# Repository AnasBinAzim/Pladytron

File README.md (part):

# **🤖 INTRODUCING TEAM PLADYTRON - WRO 2025**
<div align="center">

</div>

## 👥 **Team PLADYTRON**

| 👤 Name               | 🎓 Institution                          | 📚 Class/Year       | 🎂 Age  |
|----------------------|-----------------------------------------|---------------------|---------|
| **Anas Bin Azim**    | Adamjee Cantonment College              | Class XII           | 17      |
| **SM Mohiuddin Sami**| Rajuk Uttara Model College              | Class XII           | 17      |

---

**Team Origin**: Bangladesh

---

## 🏅 Achievements

- 🥇 **Champion, WRO Bangladesh 2024 (Future Engineers)**
- 🌍 20th place **WRO International in Izmir, Turkey**
- 🛠 Multiple national awards in robotics, AI, and competitive programming contests

---

### 🌟 **The Meaning Behind PLADYTRON**

Our team, “PLADYTRON,” is a perfect blend of technology and imagination—think of Ultron if he had a heart (and wasn’t trying to destroy the world). Inspired by the advanced intelligence of Ultron, we aim to create something truly powerful—but with a lot less existential dread and world domination plans. Plady, on the other hand, is our grounding force, a reminder that even in the world of high-tech innovation, we still know how to laugh, learn, and—let's be honest—mess up a few things along the way.
Behind every project, every line of code, there’s an unseen force—kind of like a secret weapon. And that weapon? The unwavering support of those who stand with us. Their belief in us, quietly powering every step, is the real secret sauce to our success. It’s like having a sidekick in a superhero movie, except instead of a cape, they offer advice, encouragement, and the occasional snack.
Pladytron isn’t just a name—it’s the heart and humor of a shared dream. It’s a place where creativity meets technology, and where the unexpected becomes possible. We’re not just building robots or software—we’re building something that (hopefully) makes the world a little better and a lot more fun. After all, even Ultron had a good idea at first, right?

---

# The Team  

## Anas Bin Azim  

**Age:** 17  

**High School:** Adamjee Cantonment College, Dhaka 

**Description:** Hi! I’m Anas from Bangladesh and this is my second WRO International season. In 2024, I had the honor of representing Team Mayerdoa Robotics at the World Robot Olympiad in Turkey, where we proudly placed 20th in the Future Engineers category. I’ve been deeply involved in robotics for over 4 years, building autonomous systems and competing in both national and international competitions. Beyond robotics, I’m passionate about programming, innovation, quizzing, traveling, and playing cricket]  

---

## Mohiuddin Sami  

**Age:** 17  

**High School:** Rajuk Uttara Model College, Dhaka 

**Description:** Hi! I’m Sayed Md. Mohiuddin Sami from Rajuk Uttara Model College. I’ve been part of the BDOI camp for 2 years and have spent the last 2 years working in robotics and WRO. In 2024, I had the chance to represent Bangladesh at the World Robot Olympiad International Finals in Turkey. I’ve also been doing competitive programming for 4 years, which has helped me grow in problem-solving and logical thinking. Outside of robotics and coding, I enjoy quizzing, traveling, and exploring new ideas.

## 🎉 Project Overview

This repository includes all files, designs, and code for **SMOKI**, our WRO 2024 robot. Below is the folder structure:
Here’s a breakdown of the project folders:

---

## 📑 Table of Contents

- [Code](./Code)  
- [Software Setup](./Software-Setup)  
- [WRO 2024 Future Engineers: Self-Driving Project](./WRO-2024-Future-Engineers-Self-Driving...)  
- [Experiments](./experiments)  
- [Model](./model)  
- [Problems and Solutions](./problemsandsolutions)  
- [Schematic](./schematic)  
- [Source (src)](./src)  
- [t-photos](./t-photos)  
- [v-photos](./v-photos)  
- [Video](./video)  
- [README.md](./README.md)  
---

## Robot Photos (All Directions)

<table>
  <tr>
    <td align="center"><b>Front</b></td>
    <td align="center"><b>Back</b></td>
  </tr>
  <tr>
    <td>
</td>
    <td>
</td>
  </tr>
  <tr>
    <td align="center"><b>Top</b></td>
    <td align="center"><b>Bottom</b></td>
  </tr>
  <tr>
    <td>
</td>
    <td>
</td>
  </tr>
  <tr>
    <td align="center"><b>Left</b></td>
    <td align="center"><b>Right</b></td>
  </tr>
  <tr>
    <td>
</td>
    <td>
</td>
  </tr>
</table>

----

---

### Mission Overview for WRO Future Engineers Rounds

<table>
  <tr>
    <td width="50%" valign="top" align="left">
      <h3>🏁 Round 1: Lap Completion</h3>
      <p>In <strong>Round 1</strong>, the robot must autonomously complete <strong>three laps</strong> on a pre-defined track. The goal of this round is for the bot to demonstrate stable navigation and precise lap tracking without any obstacle avoidance requirements.</p>
      <ul>
        <li><strong>Objective</strong>: Complete three laps on the track within the allotted time.</li>
        <li><strong>Key Tasks</strong>: Accurate path-following, speed control, and lap counting.</li>
      </ul>
      <div align="center">
        <br><br><br><br><br>
        
      </div>
    </td>
    <td width="50%" valign="top" align="left">
      <h3>🏆 Round 2: Lap Completion with Obstacle Avoidance and Parking</h3>
      <p>In <strong>Round 2</strong>, the bot must complete <strong>three laps</strong> while avoiding green and red obstacles:</p>
      <ul>
        <li><strong>Green Obstacles</strong>: The bot should move <strong>left</strong> to avoid.</li>
        <li><strong>Red Obstacles</strong>: The bot should move <strong>right</strong> to avoid.</li>
      </ul>
      <p>After completing the laps, the bot must accurately park within a designated zone.</p>
      <ul>
        <li><strong>Objective</strong>: Complete three laps, avoid obstacles, and park in the designated area.</li>
        <li><strong>Tasks</strong>: Obstacle detection, color-based avoidance, and precision parking.</li>
      </ul>
      <div align="center">
        
      </div>
    </td>
  </tr>
</table>

---
>[!IMPORTANT]
>**Important: WRO Future Engineers Rulebook**
>* **Thorough Reading:** Ensure that you thoroughly read the **WRO Future Engineers 2024 Rulebook** to understand all rules and guidelines.
>* **Official Link:** Access the rulebook here: [🔗 WRO Future Engineers 2024 Rulebook](https://wro-association.org/competitions/future-engineers/).

---
---

## 🧩 Components and Hardware
Our bot is equipped with various components that support its autonomous functionality. Here is a breakdown of the key hardware elements used in this project:

| Component                  | Description                                                                                      | Image                          | Purchase Link                                                                                  |
|----------------------------|------------------------------------------------------------------------------------------------|--------------------------------|-----------------------------------------------------------------------------------------------|
| **Chassis - Custom Made**   | Custom-designed chassis tailored to fit all components and optimize stability and movement.    | <div align="center"></div>         | N/A                                                                                           |
| **RPLIDAR C1**             | 360-degree laser scanner used for mapping and obstacle detection.                              | <div align="center"></div>                   | [Purchase RPLIDAR C1](https://www.mybotshop.de/SLAMTEC-RPLIDAR-C1-360-Laser-Scanner-12-m)     |
| **Servo Motor SG90**       | Small, lightweight servo motor used for precise control of angles and positioning.             | <div align="center"></div>             | [Purchase SG90](https://bongotech.ai/product/sg90-micro-servo-motor-180-degree)                |
| **SJ CAM C200**            | Captures visual data, supporting navigation and obstacle detection tasks.                      | <div align="center"></div>                  | [Purchase SJ CAM C200](https://amzn.to/3SJCAM) (From previous knowledge)                      |
| **Buck Module XL4016**     | Provides stable voltage regulation for power management.                                      | <div align="center"></div>           | [Purchase XL4016](https://amzn.to/4xl4016) (From previous knowledge)                          |
| **Motor Driver L293D**     | Dual H-Bridge motor driver for controlling DC motors and stepper motors.                       | <div align="center"></div>           | [Purchase L293D](https://electropeak.com/l293d-motor-drive-shield)                            |
| **Booster Module 5V to 40V** | Voltage booster module to step up power supply from 5V to 40V, supporting high-voltage requirements. | <div align="center"></div>       | [Purchase Booster Module](https://robu.in/product-category/electronic-modules/electronic-module/buck-boost-converter/boost-converter/) |

# Mobility Management :

#### 🛠️ Chassis Assembly Process

## CHASSIS FIRST FLOOR : 

This is the first floor of the robot chassis, designed to serve as the primary structural layer of the bot. The STL model shows a flat base plate with multiple precisely positioned mounting holes and slots for components.

Key Features:

Steering Shaft Mount: The elongated slot at the top center is designed to hold the steering shaft, ensuring smooth and stable movement.

Servo Motor Mount: Dedicated mounting holes allow the servo motor to be securely attached for steering control.

Camera Holder: The central cut-out and surrounding structure provide space for installing a camera for vision-based navigation.

Wheel Mounts: Side holes are aligned to support the wheels, making them properly fixed to the frame.

Base Support: This floor acts as the foundation of the robot, supporting the upper floors and ensuring stability during operation.

Dimensions:

Width (X): 101.5 mm

Length (Y): 185.0 mm

Thickness (Z): 10.0 mm

---
---

### CHASSIS STEERING :

This is the steering plate of the robot chassis, designed to integrate with the first floor and provide precise steering control. The central rectangular gap is a servo clearance slot, which allows the servo horn and linkage to move freely during steering. The smaller holes around the center are meant for mounting the servo securely, while the larger side holes provide attachment points to connect the steering plate with the rest of the chassis. The plate is compact yet durable, ensuring stability during turns, and it directly connects the servo motor to the steering shaft and wheels, making it an essential component for controlling the robot’s movement.

Dimensions:

Width (X): 96.2 mm

Height (Y): 35.55 mm

Thickness (Z): 10 mm

---
---

### STEERING SHAFT :

This part is the steering shaft of the robot chassis. It connects directly to the steering plate and transmits the motion from the servo motor to the wheels, enabling controlled directional movement. The design includes a central body with mounting cut-outs and side holes that allow it to be fixed securely to the chassis while maintaining free rotational movement where needed. Its sturdy build ensures that torque from the servo is effectively transferred to the wheels without bending or slipping, making it a key component for precise steering.

Dimensions:

Width (X): 

Height (Y): 

Thickness (Z): 

---
---

## CHASSIS SECOND FLOOR :

This is the second floor of the robot chassis, designed to mount the following components:

RPLIDAR C1 (with a 10 cm clearance ensured by floor orientation)

LiPo 1500mAh 9A 3S battery

STL Dimensions: 131.27 mm × 101.50 mm × 10.00 mm

The plate includes cutouts for weight reduction and cable management, along with mounting holes for secure installation. Its orientation was carefully adjusted to provide the RPLIDAR with optimal clearance for unobstructed 360° scanning.

---

## CHASSIS TOP FLOOR:

Top & 3rd Floor – Electronics Section

This floor of the chassis holds the core electronic components required for power regulation and motor control.

Components

Raspberry Pi 4B – Acts as the main controller, handling computation, control logic, and communication.

XL4016 Buck Converter – Steps down the LiPo battery voltage to the levels required by the Raspberry Pi and other electronics.

L293D Motor Driver – Provides motor control by supplying the necessary current and voltage to the DC motors.

Power Switch – Allows safe shutdown and startup of the electronics.

Veroboard – Serves as the wiring platform, connecting the Raspberry Pi, buck converter, motor driver, and switch.

Functionality

The LiPo battery powers the system.

The buck converter regulates the voltage for stable Raspberry Pi operation.

The L293D motor driver interfaces between the Raspberry Pi and the motors, enabling directional control.

The veroboard ensures secure and organized wiring between all components.

The switch provides overall power control for the floor.

---
---

>[!IMPORTANT]
> ALL THE STL AND DXF FILES ARE PROVIDED IN THE MODEL SECTION AND A PREVIEW OF THE WHOLE THING COMBINED IS GIVEN BELOW.
---

# TOTAL PREVIEW:

## Model Views

<table>
  <tr>
    <td align="center"><b>Top</b></td>
    <td align="center"><b>Bottom</b></td>
  </tr>
  <tr>
    <td>

</td>
    <td>
</td>
  </tr>
  <tr>
    <td align="center"><b>Left</b></td>
    <td align="center"><b>Right</b></td>
  </tr>
  <tr>
    <td>
</td>
    <td>
</td>
<tr>
    <td align="center"><b>Tilt1</b></td>
    <td align="center"><b>Tilt2</b></td>
  </tr>
  <tr>
    <td>
</td>
    <td>

</td>
  </tr>

</table>

---
---

# Mobility Management:

The mobility system of our robot has been meticulously designed to ensure smooth, efficient, and reliable movement, addressing both power distribution and maneuverability. This section outlines the evolution of our robot's mobility systems, including upgrades to the steering and gear systems.

---

#### **16GA 800 RPM DC Gear Motor**

<table>
<tr>
<td width="50%">
<div align="center">

</div>
</td>
<td width="50%">

A **16GA DC gear motor** is a DC motor with an integrated gearbox. It provides controlled shaft rotation with increased output torque through gearbox reduction.

##### **How the Motor Works**
- The DC motor converts electrical input into rotational motion of the armature and shaft.  
- The gearbox stages reduce output speed and increase torque at the output shaft.  
- The D-flat on the shaft provides a positive mechanical interface for gears, pulleys, or couplings.

##### **Specifications**
- **Rated Speed:** 800 RPM  
- **Shaft Diameter:** 3.0 mm (D-flat: 2.5 mm)  
- **Gearbox Diameter:** 16 mm  
- **Gearbox Length:** 14 mm  
- **Motor Body Length:** 26.5 mm  
- **Shaft Length (protruding):** 11.2 mm

##### **Advantages**
1. **Compact Design**: Small gearbox diameter and short overall length for tight assemblies.  
2. **Increased Torque**: Gear reduction delivers higher torque at the output shaft for loaded conditions.  
3. **Positive Shaft Interface**: D-flat prevents rotary slip when fitted with set-screws or couplings.

</td>
</tr>
</table>

---

### **Rear Axle Power Distribution**

Initially, the rear wheels were powered through a **Bevel Gear**, but we later upgraded to a **Differential Gearbox** to improve efficiency and performance during turns.

---

#### **Bevel Gear**

<table>
<tr>
<td width="50%">
<div align="center">
  
</div>
</td>
<td width="50%">

A **bevel gear** is a type of gear where the axes of the two shafts intersect, and the tooth-bearing faces of the gears are conical. Bevel gears are commonly used to transfer motion between intersecting shafts at an angle, typically 90°.

##### **How Bevel Gears Work**
- A driver gear transfers motion to a driven gear, which rotates an output shaft.
- The teeth of the gears are designed to mesh smoothly, transferring torque efficiently between the shafts.

##### **Advantages of Bevel Gears**
1. **Compact Design**: Suitable for space-constrained applications.
2. **Efficient Torque Transfer**: Provides reliable power transmission at angles.
3. **Versatility**: Can operate at angles other than 90° if needed.

</td>
</tr>
</table>

---
>[!IMPORTANT]
> Bevel gears were essential in the initial stages of our design, but they had limitations in terms of energy efficiency during turns.
---

#### **Differential Gearbox**

<table>
<tr>
<td width="50%">

A **differential gearbox** allows the wheels on the same axle to rotate at different speeds while receiving power from a single motor. This is crucial for smooth turning, where the outer wheel must travel a larger distance than the inner wheel.

##### **Advantages of Differential Gearbox**
1. **Smooth Turns**: Adapts to varying wheel speeds, ensuring efficient cornering.
2. **Energy Efficiency**: Reduces energy wastage by minimizing wheel slippage.
3. **Component Longevity**: Minimizes wear on tires and axles.

##### **How Differential Gears Work**
- Power from the motor is delivered to an input shaft.
- The differential splits the torque between the two wheels via bevel or spider gears inside the housing.
- During turns, the differential allows one wheel to spin faster than the other, ensuring smooth movement.

</td>
<td width="50%">
<div align="center">
  
</div>
</td>
</tr>
</table>

---

### **Servo Motor with L293D Motor Driver**

<table>
<tr>
<td width="30%">
<div align="center">
  
</div>
</td>
<td width="70%">

We used the **L293D Motor Driver** in combination with a **Servo Motor** to control the robot's wheels effectively. The L293D is a dual H-Bridge motor driver that is perfectly suited for the LEGO motor, which operates at **750mA** current.

##### **Why L293D?**
- **Optimal Current Capacity**: Can handle up to **1A** peak current, suitable for the LEGO motor’s 750mA requirement.
- **Bidirectional Control**: Facilitates forward and backward motion of the wheels.
- **Compact and Lightweight**: Ideal for small-scale robotic systems.
- **PWM Support**: Enables smooth speed control of the motors.

##### **Advantages of the Servo Motor with L293D**
1. **Accurate Steering**: The servo motor ensures precise angle adjustments.
2. **Smooth Speed Control**: PWM functionality provides variable speed control.
3. **Efficient Current Management**: Matches the LEGO motor's current needs, ensuring reliable operation.

</td>
</tr>
</table>

---

#### **Comparison: Bevel Gear vs. Differential Gearbox**

| **Feature**                | **Bevel Gear**                            | **Differential Gearbox**                |
|----------------------------|-------------------------------------------|-----------------------------------------|
| **Turning Efficiency**     | Limited; fixed wheel speeds.             | Superior; wheels rotate independently. |
| **Energy Usage**           | Higher due to slippage during turns.     | Lower; optimized for dynamic turns.    |
| **Durability**             | Higher strain on components.             | Reduced strain; longer component life. |

---

### **Steering Systems**

The robot was first designed with an Ackermann Steering System, which is widely recognized for its efficiency in full-scale vehicles where smooth and realistic cornering is important. This system was chosen because it closely replicates how cars steer, making it ideal for projects that aim to simulate real-world vehicle dynamics. However, as the design of the robot progressed, the steering system was later replaced with a LEGO-based steering mechanism. The change was made to simplify construction, reduce complexity, and improve modularity, all while maintaining effective and reliable steering control. The LEGO steering setup makes it easier to experiment, repair, and scale the design without sacrificing too much performance, which is an important advantage in prototyping and educational robotics.

The Ackermann Steering System itself is a clever mechanical arrangement that ensures each wheel follows a natural path while the vehicle turns. In any cornering situation, the inner wheels of a vehicle must rotate at a sharper angle than the outer wheels because they travel along a smaller radius. Without this adjustment, wheels would slip or drag, leading to wasted energy and uneven motion. The Ackermann geometry solves this by connecting the front wheels through steering arms angled in such a way that the imaginary extension of these arms intersects at the center of the turn’s radius. This alignment ensures that all wheels follow concentric paths, allowing the vehicle to turn smoothly and efficiently without excessive tire wear or unnecessary power loss.

In practice, the Ackermann system has several clear advantages for robotic applications. It minimizes slippage between the wheels and the ground, which results in more efficient turning and better energy conservation. The reduction of wheel drag also means that the motors driving the vehicle consume less power during maneuvers, which is especially valuable in battery-powered robots where energy efficiency extends operating time. Another key benefit is that it provides a highly realistic simulation of how cars steer, making it particularly useful for robotics projects that aim to mimic real-world automotive systems or serve as educational platforms to demonstrate fundamental vehicle dynamics. Although our project ultimately transitioned to a LEGO-based steering approach for modularity and ease of construction, the principles and advantages of Ackermann steering remain highly relevant for anyone interested in understanding efficient and practical steering systems in robotics and beyond.

---
---

## **SERVO MOTOR :** 
# Servo Motor - Tower Pro MG90S

<table>
  <tr>
    <td>
      
    </td>
    <td>
      <h3>Specifications</h3>
      <ul>
        <li><strong>Weight:</strong> 13.4g</li>
        <li><strong>Stall torque:</strong> 2.2 kgf·cm (6V)</li>
        <li><strong>Operating speed:</strong> 0.08 s/60° (6V)</li>
        <li><strong>Rotation angle:</strong> 120°</li>
        <li><strong>Gear type:</strong> Metal gears</li>
        <li><strong>Operating voltage:</strong> 4.8V – 6V</li>
      </ul>
    </td>
  </tr>
</table>

---

The Tower Pro MG90S is a micro servo motor designed for applications where compact size and high torque are required, making it a reliable choice for robotics, RC models, and automation projects. Built with durable metal gears, it offers a longer operational lifespan compared to plastic-geared alternatives, while maintaining a lightweight 13.4g profile that makes it easy to integrate into small-scale designs. Operating on a voltage range of 4.8V to 6V, it delivers up to 2.2 kgf·cm stall torque and a quick 0.08s/60° response at 6V, ensuring both strength and speed for demanding tasks. With a rotation range of 120°, the MG90S provides precise angular control suitable for robotic arms, pan-tilt camera gimbals, or steering systems in miniature vehicles. Its compatibility with standard PWM signals means it can be driven directly by most microcontrollers, including Arduino and Raspberry Pi, without the need for additional hardware. Engineers and hobbyists often choose the MG90S because it balances performance and durability in a very small form factor, making it a practical and cost-effective solution for projects that require accurate movement and dependable performance under continuous load.

---

## Where to Buy

You can purchase the servo motor here:  
👉 [Tower Pro MG90S - Cleste.ro](https://cleste.ro/motor-servo-mg90s-180g.html)

## SERVO-HOLDER :

### SG90 / MG90 Servo Holder

This is a **servo motor holder/mount** designed for **SG90** and **MG90S micro servos**.  
It provides a secure and stable way to fix the servo motor onto different surfaces such as a robot chassis, acrylic base, or wooden frame.

---

## Description
## Servo Motor Holder / Mount (SG90 & MG90S)

This servo motor holder is designed specifically for the popular SG90 and MG90S micro servos, providing a secure and reliable way to mount the motor onto different surfaces such as a robot chassis, acrylic base, or even wooden frames. The primary goal of the mount is to eliminate instability and vibration, ensuring that the servo can deliver accurate and repeatable movements during operation. For small-scale robotics and automation projects where precision matters, this holder becomes an essential accessory.
The base of the mount is a flat rectangular plate equipped with four mounting holes that allow it to be firmly attached using screws or bolts. This rigid foundation ensures that once the holder is installed, it remains stable and does not shift under load, even when the servo is driving linkages or mechanical arms. At the center of the design, there is a servo housing slot carefully dimensioned to snugly fit SG90 and MG90S servos. This slot prevents any side-to-side play and keeps the servo perfectly aligned, which is important when the servo is used for steering mechanisms, grippers, or robotic arms where accuracy of angular motion is critical.
On the sides of the housing are clamp sections with additional screw holes, which allow the servo to be tightly locked in place once inserted. This design makes sure the servo remains fixed during continuous operation, preventing unwanted movement that could lead to mechanical inaccuracy or wear. At the front, the mount features an open clearance space that allows the servo horn or arm to rotate freely without obstruction. This ensures that the servo’s full range of motion can be utilized, whether it is controlling wheels, levers, or pan-tilt systems.

The bottom of the mount is left open to provide space for the servo’s wiring to pass through. This prevents cable bending and stress at the connector, reducing the risk of damage to the wires over time and allowing easy integration into compact robotic builds. By providing both mechanical stability and practical cable management, the holder is designed to extend the lifespan of the servo and improve overall reliability of the system.

In terms of material, PLA is often sufficient for hobby projects where light loads and indoor conditions are expected. However, for applications requiring greater durability or exposure to outdoor environments, PETG or ABS is recommended since both materials offer improved toughness and resistance to stress compared to PLA. The mount’s design is fully compatible with Tower Pro SG90 and MG90S servos, making it versatile for use across a wide range of robotic and automation projects where these micro servos are commonly deployed.

---
---
# ⚡ Power and Sense Management

The **Power and Sense Management** system of our robot has been meticulously designed to optimize performance while ensuring reliable power delivery, precise sensing, and efficient communication between components.
# Battery: Gens Ace Airsoft 3S Li-Po Battery (11.1V 1500mAh 35C)

<table>
  <tr>
    <td>
      
    </td>
    <td>
      <h3>Specifications</h3>
      <ul>
        <li><strong>Brand:</strong> Gens Ace Airsoft</li>
        <li><strong>Battery Type:</strong> Li-Po (Lithium Polymer)</li>
        <li><strong>Nominal Voltage:</strong> 11.1V (3S)</li>
        <li><strong>Capacity:</strong> 1500 mAh</li>
        <li><strong>Energy:</strong> 16.65 Wh</li>
        <li><strong>Discharge Rate:</strong> 35C</li>
        <li><strong>Connector Type:</strong> T-Plug / Deans Connector</li>
        <li><strong>Balance Plug:</strong> JST-XH</li>
        <li><strong>Weight:</strong> ~120g</li>
      </ul>
    </td>
  </tr>
</table>

---

The **Gens Ace 3S Li-Po battery** is a lightweight and powerful energy source designed for high-performance robotics, drones, RC vehicles, and airsoft equipment.  
With a **capacity of 1500mAh** and a **35C discharge rating**, it delivers consistent current output suitable for motors, sensors, and controllers that require stable power.  
Its **compact size and low weight** make it easy to integrate into mobile robotic platforms.  
The built-in **Deans/T-Plug connector** ensures low-resistance power delivery, while the **JST-XH balance connector** allows for safe charging and cell balancing.  

This battery is ideal for applications requiring **high burst currents, reliability, and long cycle life**, making it a solid choice for powering small-to-medium robotics systems.

---

# **Microcontroller :**  
# Raspberry Pi 4 Model B

<table>
  <tr>
    <td>
      
    </td>
    <td>
      <h3>Specifications</h3>
      <ul>
        <li><strong>Processor:</strong> Broadcom BCM2711, Quad-core Cortex-A72 (ARM v8) 64-bit SoC @ 1.5GHz</li>
        <li><strong>RAM Options:</strong> 2GB, 4GB, or 8GB LPDDR4-3200 SDRAM</li>
        <li><strong>Networking:</strong> Gigabit Ethernet, 2.4GHz & 5.0GHz 802.11ac Wi-Fi, Bluetooth 5.0</li>
        <li><strong>USB Ports:</strong> 2 × USB 3.0, 2 × USB 2.0</li>
        <li><strong>Video & Sound:</strong> 2 × micro-HDMI ports (up to 4Kp60), MIPI DSI display port, MIPI CSI camera port</li>
        <li><strong>Storage:</strong> microSD card slot for OS and data storage</li>
        <li><strong>GPIO:</strong> 40-pin header, backward-compatible with previous Raspberry Pi boards</li>
        <li><strong>Power:</strong> 5V DC via USB-C connector (minimum 3A)</li>
        <li><strong>Dimensions:</strong> 85.6mm × 56.5mm</li>
      </ul>
    </td>
  </tr>
</table>

---

The **Raspberry Pi 4 Model B** is a powerful single-board computer that serves as the main controller of the robot.  
It offers significant improvements over previous models, including a faster **quad-core ARM Cortex-A72 CPU**, more memory options, dual micro-HDMI outputs supporting **dual 4K displays**, and faster networking with **true Gigabit Ethernet** and **dual-band Wi-Fi**.  
Its 40-pin GPIO header provides compatibility with a wide range of sensors, motor drivers, and other modules, making it extremely versatile for robotics and IoT applications.  

Thanks to its **USB 3.0 ports**, it can interface with high-speed peripherals such as cameras, LIDAR sensors, or external storage, while the **USB-C power input** ensures stable operation.  
In this project, the Raspberry Pi 4B acts as the **central brain**, handling computer vision, path planning, and high-level decision-making, while coordinating with microcontrollers, sensors, and actuators to control the entire robot.

---

## **GPIO PINOUT OF RPI 4B** : 

# Raspberry Pi 4 Model B GPIO (40-pin Header)

<table>
  <tr>
    <td>
      
    </td>
    <td>
      <h3>Specifications</h3>
      <ul>
        <li><strong>Total Pins:</strong> 40 (2×20 header)</li>
        <li><strong>Power Pins:</strong> 2 × 5V, 2 × 3.3V, 8 × Ground (GND)</li>
        <li><strong>GPIO Pins:</strong> 26 (configurable as input/output)</li>
        <li><strong>Dedicated Interfaces:</strong> 
          <ul>
            <li>UART (TXD, RXD)</li>
            <li>SPI (MOSI, MISO, SCLK, CE0, CE1)</li>
            <li>I²C (SDA, SCL)</li>
            <li>PWM channels</li>
          </ul>
        </li>
        <li><strong>Voltage Levels:</strong> 3.3V logic (NOT 5V-tolerant)</li>
        <li><strong>Backward Compatibility:</strong> Same pinout as Raspberry Pi 3B/3B+</li>
      </ul>
    </td>
  </tr>
</table>

---

The **Raspberry Pi 4B GPIO header** provides 40 pins that allow direct hardware interfacing with sensors, actuators, and external modules.  
Among these are multiple **power pins (5V and 3.3V)**, **ground pins**, and **26 flexible GPIO pins** which can be programmed as input or output using libraries such as **RPi.GPIO** or **GPIO Zero**.  

The header also exposes dedicated hardware interfaces, including **UART for serial communication**, **SPI for high-speed device connections**, and **I²C for multi-sensor integration**, along with PWM support for driving **motors, LEDs, and servos**.  

Because the pins operate at **3.3V logic levels**, external level shifters are required when interfacing with 5V components.  
This GPIO header is the bridge between the Raspberry Pi and the physical world, making it an essential feature for robotics, IoT, and embedded system projects.

---
---

## **BUCK CONVERTER** (8.4 TO 5V) : 
### XL4016 DC-DC Step-Down Module

<table>
  <tr>
    <td>
      
    </td>
    <td>
      <h3>Specifications</h3>
      <ul>
        <li><strong>Chipset:</strong> XL4016E1 DC-DC Buck Converter</li>
        <li><strong>Input Voltage:</strong> 8V – 36V DC</li>
        <li><strong>Output Voltage:</strong> 1.25V – 32V DC (adjustable)</li>
        <li><strong>Output Current:</strong> Up to 8A (continuous), 12A peak</li>
        <li><strong>Conversion Efficiency:</strong> Up to 95%</li>
        <li><strong>Switching Frequency:</strong> ~180 kHz</li>
        <li><strong>Protections:</strong> Over-current, thermal shutdown</li>
        <li><strong>Heat Dissipation:</strong> Integrated heatsink for stability under high load</li>
        <li><strong>Dimensions:</strong> 60mm × 52mm × 20mm (approx.)</li>
      </ul>
    </td>
  </tr>
</table>

---

The **XL4016 buck converter** is a high-power DC–DC step-down module designed to provide stable and efficient voltage regulation for robotics, automation, and embedded systems. With an input range of 8–36V and an adjustable output from 1.25–32V, it is highly versatile and can power a wide variety of subsystems from a single battery source. Its ability to deliver up to **8A of continuous current** (with peaks of 12A) makes it suitable for driving motor controllers, Raspberry Pi boards, and other current-hungry electronics simultaneously. The module achieves up to 95% efficiency, reducing energy losses and minimizing heat buildup. The integrated heatsink ensures stable operation even under heavy loads, while built-in protection circuits safeguard against over-current and thermal issues. For robotics applications, the XL4016 is often recommended because it allows a single Li-Po or Li-ion battery pack to be safely stepped down to multiple regulated voltages, ensuring reliable operation of both logic-level electronics and power-hungry actuators.

---

## **Sensor :**  
# MPU-6050 6-Axis Gyroscope and Accelerometer

<table>
  <tr>
    <td>
      
    </td>
    <td>
      <h3>Specifications</h3>
      <ul>
        <li><strong>Chipset:</strong> InvenSense MPU-6050</li>
        <li><strong>Sensor Type:</strong> 3-axis gyroscope + 3-axis accelerometer</li>
        <li><strong>Operating Voltage:</strong> 3V – 5V</li>
        <li><strong>Communication Interface:</strong> I²C (default address 0x68)</li>
        <li><strong>Gyroscope Range:</strong> ±250, ±500, ±1000, ±2000 °/s</li>
        <li><strong>Accelerometer Range:</strong> ±2g, ±4g, ±8g, ±16g</li>
        <li><strong>Sampling Rate:</strong> Up to 1 kHz</li>
        <li><strong>Digital Motion Processor (DMP):</strong> Built-in for sensor fusion</li>
        <li><strong>Dimensions:</strong> ~20mm × 15mm × 2mm (module size varies)</li>
      </ul>
    </td>
  </tr>
</table>

---

The **MPU-6050** is a 6-axis motion tracking sensor that integrates a **3-axis gyroscope** and a **3-axis accelerometer** on a single chip, making it one of the most widely used sensors in robotics and embedded systems. It communicates via the I²C protocol, which allows it to connect easily to microcontrollers like the Arduino, ESP32, or Raspberry Pi. The sensor provides motion data across multiple selectable ranges, with gyroscope sensitivity from ±250 to ±2000 degrees per second and accelerometer ranges from ±2g to ±16g. This versatility makes it suitable for detecting orientation, angular velocity, and linear acceleration in real time. The built-in **Digital Motion Processor (DMP)** can handle sensor fusion internally, combining gyro and accelerometer data to output stable orientation values, reducing the computational load on the main controller. For robotics, the MPU-6050 is commonly used in balancing robots, drones, navigation systems, and motion-controlled projects, where accurate and responsive motion sensing is essential for stability and control.

---

## **Camera :**  
# SJCAM C200 Action Camera

<table>
  <tr>
    <td>
      
    </td>
    <td>
      <h3>Specifications</h3>
      <ul>
        <li><strong>Sensor:</strong> 4K CMOS image sensor</li>
        <li><strong>Video Resolution:</strong> 4K @ 24fps, 2K @ 30fps, 1080p @ 60fps</li>
        <li><strong>Photo Resolution:</strong> Up to 16MP</li>
        <li><strong>Lens:</strong> 154° wide-angle lens</li>
        <li><strong>Display:</strong> 1.3-inch front screen + status indicators</li>
        <li><strong>Battery:</strong> 1200mAh (removable, USB-C charging)</li>
        <li><strong>Connectivity:</strong> Wi-Fi, USB-C</li>
        <li><strong>Storage:</strong> MicroSD card up to 128GB</li>
        <li><strong>Waterproof:</strong> Up to 5m without case, 30m with case</li>
        <li><strong>Dimensions:</strong> ~68mm × 32mm × 26mm</li>
      </ul>
    </td>
  </tr>
</table>

---

The **SJCAM C200** is a compact 4K action camera designed for high-quality video and photo capture in robotics, drones, and field-testing environments. It features a **154° wide-angle lens**, making it well-suited for wide field-of-view applications such as navigation, mapping, and vision-based obstacle detection. The camera supports recording at multiple resolutions, including **4K at 24fps** and **1080p at 60fps**, giving flexibility between image detail and frame rate depending on the task. With a removable **1200mAh battery** and **USB-C charging**, it provides convenient power management, while Wi-Fi connectivity allows real-time preview and data transfer to companion devices. Its rugged design makes it waterproof up to 5m without housing and up to 30m with an additional case, ensuring reliable performance in outdoor and challenging environments. For robotics projects, the SJCAM C200 is an excellent choice as a vision module, balancing portability, durability, and high-definition imaging in a small and versatile package.
---
---

# *PCB*  
## Previous PCB Design and Power Distribution  

| **Top View of PCB** | **Bottom View of PCB** | **Power Management Diagram** |
|----------------------|------------------------|-------------------------------|
|  |  |  |

---

The PCB shown above was designed as the **central power management and distribution unit** for the robot, ensuring that every subsystem received the correct voltage and current for stable operation. The board draws power from two **Lithium-Ion cells**, each rated at 4.2V, providing a combined supply of **8.4V** when fully charged. This input is then carefully regulated using multiple DC–DC converters to meet the diverse requirements of the system.  

At the heart of the regulation stage, an **XL4016 buck converter** steps the 8.4V battery voltage down to a stable **5V rail**, which powers the **Raspberry Pi 5** and other core electronics. Additional buck converter modules are integrated to provide subsystem-specific voltages: one module regulates to **6V for the servo motor**, while another supplies **5V dedicated to the ESP32 microcontroller**, ensuring isolation and consistent operation. For the high-power motors, the PCB incorporates a **buck-boost converter** that outputs **12V**, guaranteeing reliable torque and speed even as the battery voltage drops during operation.  

This combination of regulated rails allows the robot to operate multiple controllers, sensors, and actuators from a single compact PCB without instability or power loss. By integrating switching converters and carefully routing the distribution, the board minimizes heat, maximizes efficiency, and protects sensitive comp
onents from voltage fluctuations. Overall, this design highlights the importance of structured power management in robotics, where both logic-level devices and power-hungry actuators must coexist seamlessly on the same platform.

---
# *CurrentPCB* :

Compared to our earlier design, the new PCB introduces several improvements aimed at stability, modularity, and ease of use. The earlier version primarily served as a basic power distribution board with buck converters and minimal control features. In this revised version, additional attention has been given to **structured wiring via ribbon connectors**, improved **switching and manual control through a larger rocker and push button**, and **better integration of the buck converter section** with heat dissipation. The placement of capacitors, inductor coil, and screw terminals has been optimized for cleaner power flow, and the routing now reduces noise and voltage drops across the board. Overall, the new design is more robust, reliable, and serviceable compared to the prototype.  

# *CIRCUITDIAGRAM* :

# Explanation:

This circuit integrates the Raspberry Pi GPIO header with a set of sensors, actuators, and motor driver modules, forming the control and power distribution system for a small robot. The Raspberry Pi acts as the central controller, sending signals to motors, servos, and indicators while also receiving sensor feedback to make decisions in real time.
At the top of the diagram, we see the Raspberry Pi GPIO pinout, which is the core interface between the Pi and external devices. Each pin can be configured as an input or output, supplying logic-level signals (3.3V) that control the connected hardware. The Pi provides 5V and 3.3V power rails, as well as ground connections, which are distributed to all modules in the circuit.
A servo motor is connected to the Pi using three wires: VCC (power), GND (ground), and the SIGNAL pin, which is linked to one of the Pi’s PWM-enabled GPIO pins. This allows the Pi to control the servo angle precisely using PWM (Pulse Width Modulation). Servos are typically used for steering mechanisms or angular adjustments in robots, so this one is likely managing the robot’s front wheel alignment or a pan/tilt system.
On the left side of the circuit, a push button and an LED are wired into the GPIO header. The push button is used as a digital input — when pressed, it connects the GPIO pin to ground, sending a low signal to the Pi. This can be used for resets, mode changes, or manual overrides. The LED, on the other hand, is controlled through a GPIO pin as an output. It provides visual feedback, such as power status, errors, or activity indicators, allowing the operator to easily monitor the robot’s state.
At the bottom, the L293D motor driver IC is connected between the Pi and a DC motor. The Pi itself cannot supply enough current to directly drive motors, so the L293D acts as a buffer and amplifier. It uses the low-current logic signals from the Pi to control the higher-current flow from the battery to the motor. This enables bidirectional motor control (forward and backward rotation) and also supports PWM for speed regulation. In this configuration, the motor shown is most likely one of the drive motors that moves the robot’s wheels.
On the right side, we see an MPU-6050 IMU (Inertial Measurement Unit) connected via I²C communication. The SDA (data) and SCL (clock) lines run from the Pi’s GPIO header to the sensor module, with VCC and GND providing power. The MPU-6050 combines a 3-axis gyroscope and a 3-axis accelerometer, which together measure angular velocity and linear acceleration. This data is essential for balance, orientation, and navigation, particularly in robots that need to track their motion or maintain stability on uneven terrain.
Next to it is a buck converter module (with a heatsink and inductor coil). This component regulates the battery voltage down to safe levels required by the Raspberry Pi, motors, and sensors. Since motors can cause voltage fluctuations when they start or stop, the buck converter ensures that the Pi always receives a clean and stable supply. The input of the buck converter comes directly from the main battery (Li-ion cells), and the outputs are distributed to different subsystems: 5V for the Pi and ESP32, 6V for the servo, and 12V (via buck-boost regulation) for the motors.
The wiring shows how all the power rails (red for positive, black for ground, and green/yellow/orange for signals) are carefully routed to prevent noise and maintain clear separation between logic-level signals and high-current motor wiring. The Pi orchestrates everything: it reads the sensor data from the MPU-6050, processes input from the push button, controls the LED for feedback, drives the servo motor with PWM, and commands the DC motor through the L293D motor driver.

---
# *SCHEMATIC FOR THE NERDS* : 

###  Camera Placement and Functionality

The robot's main camera is positioned at the top and angled slightly downwards. This setup enhances object detection capabilities by providing:
- **🔍 Close-Range Detection**: The camera can identify objects in close proximity with high accuracy.
- **🌐 Extended-Range Detection**: Ensures objects further away are detected effectively.

The camera feeds data to the **Raspberry Pi 4**, which processes image recognition algorithms to detect towers and corner lines. The processed data is then transmitted to the **ESP32 microcontroller** for real-time navigation and obstacle avoidance.

---

>[!IMPORTANT]
> **Power Highlights:**
> - The XL4016 Buck Converter ensures stable voltage regulation, critical for protecting the Raspberry Pi and ESP32 microcontroller during operation.
> - Independent buck modules handle the servo motor and ESP32 power needs, optimizing energy usage across all components.

---
---

## Power Regulation and Control PCB

This PCB is a custom-made prototyping board that acts as the main power regulation and control hub of the robot. It integrates a red rocker switch as the primary ON/OFF control, a large red push button for reset or emergency stop functions, and a green LED that indicates when the system is active. Flat ribbon cables connect the board to the Raspberry Pi or Arduino, carrying essential GPIO signals. The lower section features a copper coil, multiple electrolytic capacitors, and MOSFETs/regulators that form a DC–DC converter, ensuring stable power delivery from the battery to different subsystems. Blue trimpots allow precise voltage calibration, while a screw terminal block provides secure connections for input and output wiring. Altogether, this PCB manages distribution, stabilization, and manual control of power, making it a central part of the robot’s electronic system.

---

#  OBSTACLE MANAGEMENT AND CODE EPXLANATION

In **Round 1**, our robot **SMOKI** must autonomously complete **three laps** on a predefined track without the need for obstacle avoidance. To achieve precise navigation and lap counting, we have developed a robust algorithm that integrates image processing with control systems.

---

###  Algorithm Overview

1. **📸 Image Acquisition**:
   - The robot captures real-time images of the track using its onboard camera.

2. **🎨 Color Space Conversion**:
   - Captured images are converted from the **RGB** color space to the **HSV (Hue, Saturation, Value)** color space.
   - The HSV color space is chosen for its effectiveness in color segmentation, as it is less sensitive to lighting variations.

3. **🔍 Color Segmentation and Orientation Determination**:
   - Using predetermined HSV ranges, the algorithm isolates the **blue** and **orange** line segments on the track.
   - During the first run, the robot checks whether the blue line appears before the orange line or vice versa.
   - **Orientation Determination**:
     - If the blue line comes before the orange line, the robot sets its orientation accordingly.
     - This initial orientation check ensures the robot follows the track in the correct direction.

4. **📏 Line Detection and Lap Counting**:
   - The **Hough Line Transform** method is applied to detect lines within the segmented images.
   - The robot counts the detected lines to keep track of laps.
   - **Lap Completion**:
     - After counting **12 lines** (corresponding to three laps), the robot initiates a predetermined delay and then stops.

5. **⚙️ Position Correction Using PID Control**:
   - Before setting the orientation, a **PID (Proportional-Integral-Derivative) controller** calculates the error.
   - **Error Calculation**:
     - The error is determined by the difference between the distances measured by sensors on the left and right sides of the robot (i.e., `error = left_distance - right_distance` or vice versa).
   - **Distance Maintenance**:
     - If the orientation is **right-based**, the robot maintains a **25 cm** distance from the right side.
     - If the orientation is **left-based**, it maintains a **25 cm** distance from the left side.
   - The PID controller adjusts the robot's steering to minimize the error, helping it stay centered on the track.

---

The process begins with image acquisition and preprocessing, where high-resolution images are captured at regular intervals to provide up-to-date visual data of the track. These images are then converted into the HSV (Hue, Saturation, Value) color space. Unlike RGB, HSV separates brightness from color information, which makes it more effective for thresholding and detecting specific colors under varying lighting conditions.
Once the images are converted, color segmentation is performed. By applying HSV thresholding, the system isolates pixels belonging to the blue and orange ranges. This allows the robot to detect both blue and orange track lines. The sequence of detected colors is also analyzed to establish the robot’s orientation at the start, ensuring it does not misinterpret direction and mistakenly count laps in reverse.
After segmentation, the system proceeds to line detection using the Hough Transform. First, preprocessing methods such as Gaussian blur and Canny edge detection are applied to enhance the visibility of edges in the image. The Hough Line Transform then detects straight lines by mapping points from image space into a parameter space, identifying lines where multiple points converge. Each detected line crossing increments a counter, and lap completion is recognized after twelve line crossings, which correspond to three full laps of both blue and orange lines combined.
To maintain correct alignment on the track, the robot employs a PID (Proportional–Integral–Derivative) control system for position correction. Distance sensors on either side of the robot provide real-time measurements of its relative position. The difference between left and right readings produces an error signal, which the PID controller minimizes. The proportional term reacts to the current error, the integral term compensates for accumulated past errors, and the derivative term predicts future error based on its rate of change. The controller’s output is translated into steering adjustments, keeping the robot centered. Depending on its orientation, the robot may also bias its movement slightly toward the left or right side of the track, ensuring consistent lap recognition and stable navigation.

## 📊 Round 1 Algorithm - Corner Detection Navigation

In Round 1 of the **Future Engineers** category, our robot follows a structured pipeline to complete a lap, detect corners, and terminate correctly at the finish line. The algorithm is designed to balance **robust line tracking** with **precise stopping conditions**.

---
# Explanation of the the first round :
The flowchart represents the logic behind a line-following robot with LIDAR support, where lap counting and orientation checks are integrated into its navigation system. Let’s walk through it in sequence.
1. Start and Image Capture
The process begins at the Start node. The robot immediately moves to capture an image from its camera. This image forms the basis for detecting whether the guiding line (blue or orange track line) is present in the current frame.
2. Checking for Line Detection
After capturing the image, the robot checks: Is a line detected?
If Yes, it proceeds to the orientation check.
If No, the robot relies on LIDAR scanning to infer the path instead.
This dual check ensures that if the camera fails to detect a line (due to noise, occlusion, or lighting issues), the LIDAR system provides redundancy.
3. Line Detected Path
If a line is found, the robot must determine whether its orientation has already been set.
If orientation is set, the system simply increments the line counter (Line Count ++), tracking how many lines have been crossed.
If orientation is not set, the robot fixes its orientation based on the detected color sequence (blue vs. orange) and also increments the line counter. This prevents mistakes in lap counting by ensuring the robot knows which direction it is traveling.
4. Lap Completion Check
Once the line count is updated, the system checks three conditions simultaneously:
LineCount ≥ 12 → meaning the robot has crossed enough lines for three full laps (each lap includes multiple blue/orange crossings).
LastLine > 1500 ms → a time gap condition that prevents double-counting if two detections happen too close together.
FloorDist < 1500 → a distance-based condition to ensure the robot is physically on the track surface and not falsely detecting lines elsewhere.
If all conditions are satisfied, the robot concludes that laps are complete, moves to Stop Bot, and terminates the code.
If not, the system moves to path correction with LIDAR and PID control.
5. No Line Detected Path
If the camera does not detect a line, the robot initiates a LIDAR scan of its surroundings. From this scan, it checks the slope of adjacent lines detected by LIDAR.
If the slope is perpendicular, this indicates the robot has crossed a track line, so the line counter is incremented and lap completion is re-evaluated.
If the slope is not perpendicular, the system assumes the robot is simply navigating without crossing a line and moves to LIDAR-based pathfinding.
This branch ensures the robot doesn’t lose track of lap progress even if the camera fails.
6. Weighted Average Pathfinding with LIDAR
When either:
the lap is not complete, or
no perpendicular crossing is found,
the system falls back to LIDAR-based navigation. Here, the robot uses a weighted average method from LIDAR readings to determine the best safe path forward (e.g., avoiding obstacles and staying centered).
7. PID Steering Correction
Once the best path is determined, the robot applies a PID controller to calculate the precise steering angle.
The error signal is generated from differences in left/right LIDAR (or distance sensor) readings.
The PID controller minimizes this error to keep the robot aligned on track.
8. Continuing Navigation
Finally, the robot applies the PID steering adjustment and continues navigating along the track until it loops back to capture the next image, repeating the cycle until the termination condition is met.
---
**Flowchart:**

```mermaid
flowchart TD
    A[Start] --> B[Capture Image]
    B --> C{Line Detected?}
    
    %% Line Detected Branch
    C -->|Yes| D{Orientation Set?}
    D -->|Yes| E[Line Count ++]
    D -->|No| F[Fix Orientation for Next Run and Line Count ++]
    E --> G{LineCount >= 12 AND LastLine > 1500ms AND FloorDist < 1500?}
    F --> G
    G -->|Yes| H[Stop Bot and Terminate Code]
    G -->|No| K[Use Weighted Average from LIDAR to Find Best Path]
    
    %% No Line Detected Branch
    C -->|No| I[LIDAR Scan Image]
    I --> J{Slope of Adjacent Lines?}
    J -->|Perpendicular| L[Line Count ++]
    J -->|Not Perpendicular| K
    L --> G
    
    %% Common Path
    K --> M[PID Calculates Steering Value]
    M --> N[Continue Navigation]

```

---

# CODE EXPLANATION :
## LIDAR CODE:

The LidarReader class provides a simple interface for capturing and storing LiDAR sensor data in real time during the robot’s first round of operation. When initialized, it starts an external LiDAR driver program as a subprocess, configured with a serial port and baud rate. A background thread continuously reads the sensor’s live output from the subprocess, line by line. Each line, containing an angle and a distance measurement, is parsed using a regular expression. The parsed results are stored in a dictionary where each angle (in degrees) is mapped to its corresponding distance value. This allows the robot to quickly access either the distance at a specific angle or retrieve all available readings at once. The stop() method cleanly terminates the subprocess when the LiDAR is no longer needed. Overall, this design ensures non-blocking, thread-safe data collection from the LiDAR, enabling the robot to maintain a constantly updated map of its surroundings during navigation.
---

## Line Checker Code:

# Geometric Line Operations

This repository contains a set of Python functions for performing geometric operations on lines. These functions are useful for tasks like checking if points lie on a straight line, determining if two lines are perpendicular, and finding the intersection of two lines. The operations rely on the `numpy`, `scipy`, and `shapely.geometry` libraries for numerical and geometric computations.

The functions include:

- **`coords(r, theta_deg)`**: Converts polar coordinates (radius `r` and angle `theta_deg` in degrees) into Cartesian coordinates (`x`, `y`). This is useful for converting data in polar form to standard Cartesian coordinates for easier geometric calculations.
  
- **`linearity(points)`**: This function checks if a set of points lies approximately on a straight line using linear regression. The function calculates the best-fit line using the `scipy.stats.linregress` function, returning a boolean indicating if the points are linear (based on an R-squared threshold), the slope and intercept of the line, and the R-squared value of the linear regression. It also handles the case of vertical lines (where all x-coordinates are the same).
  
- **`are_perpendicular(m1, m2)`**: This function checks whether two lines with slopes `m1` and `m2` are perpendicular. For two lines to be perpendicular, the product of their slopes should be `-1`. The function also handles special cases where one or both lines are vertical (undefined slopes), as vertical lines have unique behavior when checking perpendicularity.
  
- **`get_intersection(m0, b0, m1, b1)`**: Given two lines, the function computes their intersection point. The lines are represented by their slopes (`m0`, `m1`) and intercepts (`b0`, `b1`). If one of the lines is vertical (slope is `None`), the function calculates the intersection accordingly. Otherwise, the intersection is found using the formula for the intersection of two lines: solving for `x` and using the result to find `y`.

### Dependencies

The functions rely on the following Python libraries:
- `numpy`: For handling numerical operations such as trigonometry and arrays.
- `scipy`: Specifically, the `scipy.stats.linregress` function is used for performing linear regression and calculating the R-squared value.
- `shapely`: A library for geometric operations (though not directly used in the provided functions, it may be part of future implementations for geometry-related tasks).

# Motor Code :

This Python class is designed to control a motor's forward and reverse rotation using the `pigpio` library. It uses PWM (Pulse Width Modulation) to control the speed of the motor, and GPIO pins on the Raspberry Pi are used to drive the motor in either direction. The class provides three primary functions: **forward**, **reverse**, and **stop**.

## Dependencies

- `pigpio`: The `pigpio` library is used to interface with the GPIO pins of the Raspberry Pi. It allows us to control the motor's direction and speed using PWM signals.

- `utility`: This imports `clamp` (and optionally `map_range`) for ensuring the speed value remains within the appropriate range (0 to 255).

## Motor Class

### `__init__(self, pi, forward_pin=12, reverse_pin=18, freq=1000)`

This is the constructor of the `Motor` class. It initializes the motor control, including setting up the GPIO pins and the PWM frequency.

#### Parameters:
- `pi`: The `pigpio.pi()` instance (already connected to the Raspberry Pi).
- `forward_pin`: The GPIO pin number for controlling the forward direction of the motor (default is pin 12).
- `reverse_pin`: The GPIO pin number for controlling the reverse direction of the motor (default is pin 18).
- `freq`: The frequency for the PWM signal (default is 1000 Hz).

### `forward(self, speed=255)`

This function runs the motor in the forward direction at a specified speed. The speed is provided as a PWM duty cycle value ranging from 0 to 255.

#### Parameters:
- `speed`: The motor speed, represented as a PWM duty cycle value. The default value is 255 (maximum speed).

The function:
- Clamps the `speed` to ensure it is between 0 and 255.
- Sets the PWM frequency for the forward direction.
- Sets the duty cycle for the forward direction pin to control the speed.
- Ensures the reverse direction pin is turned off.

### `reverse(self, speed=255)`

This function runs the motor in the reverse direction at a specified speed. Like the `forward()` function, it uses a PWM duty cycle value between 0 and 255 to control speed.

#### Parameters:
- `speed`: The motor speed, represented as a PWM duty cycle value. The default value is 255 (maximum speed).

The function:
- Clamps the `speed` to ensure it is between 0 and 255.
- Sets the PWM frequency for the reverse direction.
- Sets the duty cycle for the reverse direction pin to control the speed.
- Ensures the forward direction pin is turned off.

### `stop(self)`

This function stops the motor completely by turning off both the forward and reverse direction pins. It sets the PWM duty cycle for both pins to 0, effectively stopping the motor.

#### Functionality:
- Sets the PWM duty cycle for both the forward and reverse pins to 0.
- Stops the motor in both directions.

---

# LIDAR READER CODE:

# LidarReader Class

This repository contains a Python class `LidarReader` designed to interface with a Lidar sensor connected via a serial port. It continuously reads data from the Lidar sensor and stores it in a dictionary, where the keys are angles and the values are the corresponding distances. The class runs the Lidar process in a background thread, ensuring non-blocking operation for continuous data reading.

## Overview

The `LidarReader` class is responsible for:
1. Launching an external Lidar binary as a subprocess.
2. Continuously reading and parsing the sensor's output (angle and distance data).
3. Storing the readings in a dictionary.
4. Providing methods to retrieve the Lidar data at specific angles or as a complete dataset.
5. Allowing the process to be terminated when no longer needed.

## Methods

### 1. `__init__(self, path, port="/dev/ttyUSB0", baud="460800")`
This is the constructor method that initializes the Lidar reader by:
- Starting the Lidar process as a subprocess.
- Setting up a background thread to continuously read and parse the Lidar output.

#### Parameters:
- `path` (str): The path to the Lidar binary (e.g., `./lidar_driver`).
- `port` (str, optional): The serial port for communication with the Lidar (default is `/dev/ttyUSB0`).
- `baud` (str, optional): The baud rate for communication (default is `460800`).

### 2. `_parse_line(self, line)`
This method takes a line of data from the Lidar output, uses a regular expression to extract the angle and distance, and returns them as a dictionary.

#### Parameters:
- `line` (str): A line of data from the Lidar output.

#### Returns:
- A dictionary with keys `"ang"` (angle) and `"dist"` (distance), or `None` if the line is malformed.

### 3. `_read_sensor_output(self)`
This method continuously reads the Lidar data in a background thread and processes each line using the `_parse_line` method. It stores the parsed angle and distance values in the `self.data` dictionary.

### 4. `get(self, angle)`
This method returns the distance corresponding to a specific angle from the Lidar data.

#### Parameters:
- `angle` (int): The angle for which the distance reading is required.

#### Returns:
- The distance at the specified angle or `None` if the angle is not found in the data.

### 5. `get_all(self)`
This method returns a copy of all current Lidar readings stored in `self.data`.

#### Returns:
- A dictionary of all the angle-distance pairs.

### 6. `stop(self)`
This method terminates the Lidar process and stops the background thread reading data.

---

# First Round Algorithm Code : The explanation is already above and you can contemplate it by seeing the flowchart too thats why not explaining here :))

# Wall Following Robot Using Lidar

This repository contains the code for a wall-following robot that uses Lidar sensor data to navigate and avoid obstacles. The robot is capable of following either the left or right wall based on the proximity detected by the Lidar sensor. It uses a servo for steering and motors for movement. The Lidar data is processed in real-time to make decisions for navigation and wall-following.

## Overview

The robot continuously reads data from a Lidar sensor to detect walls on the left and right. Based on the proximity of the walls, the robot adjusts its movement to follow the closer wall. It uses Lidar data to check for straight lines, intersections, and to ensure it follows the path correctly. If the robot detects an obstacle or a sharp turn, it adjusts its path accordingly.

## Features

- **Lidar-based Navigation**: The robot uses Lidar data to measure distances and detect walls on the left and right.
- **Wall Following**: The robot can follow either the left or right wall depending on which is closer.
- **Geometric Calculations**: The program uses linear regression to check if points form straight lines and calculates intersections for navigation.
- **Servo Steering**: The robot's steering is controlled using a servo, which adjusts based on Lidar readings.
- **Motor Control**: Motors are used for forward movement, with speed controlled by PWM (Pulse Width Modulation).

## How It Works :
## Initialization
## LidarReader: The LidarReader class interfaces with the Lidar sensor to continuously read distance data from various angles.
## Motor: The Motor class controls the movement of the robot.
## Servo: The Servo class controls the robot's steering mechanism based on the Lidar data.
## Wall Detection and Decision Making
## The robot continuously checks the distances to the left and right walls using the Lidar sensor. Based on which wall is closer, the robot decides which wall to follow:

## This is the stopping condition.

#  Round 2 Algorithm - Lap Completion with Obstacle Avoidance and Object Detection

Round 2 involves an enhanced version of our robot SMOKI, which autonomously completes three laps, avoiding obstacles and calculating the steering value based on object prioritization and boundary detection. Below is an in-depth look at the step-by-step algorithm implemented for this round.

##  Step-by-Step Algorithm Overview

###  Image Acquisition:
- The camera captures real-time images of the track and surroundings.

###  HSV Color Conversion:
- Convert the captured image from RGB to HSV (Hue, Saturation, Value) scale.
- Store all relevant line and object colors for further use.

###  Gaussian Blur:
- Apply Gaussian Blur to the frame to reduce noise.
- Based on predetermined HSV range, isolate the black border portion.

###  Black Border Detection:
- Use Canny Edge Detection to identify the black border walls.
- Apply Hough Line Probabilistic Transformation to determine acceptable border walls.

###  Border Masking:
- Create a border in the frame based on the detected lines.
- Mask out everything beyond the border to eliminate unnecessary information for the rest of the algorithm.

###  Line Detection (Blue or Orange):
- Identify lines using the predetermined HSV color range.
- Check for the blue or orange line in the frame.

### Slope Calculation:
- If a line is found, calculate the minimum and maximum slopes for both the blue and orange lines (if both are present).

###  Orientation Determination:
- If both blue and orange lines are detected, compare their slopes.
- Determine the clockwise or anti-clockwise orientation and store this in a variable for future reference.

###  Object Detection and Prioritization:
- Detect acceptable objects within the boundary wall.
- Assign a priority value to each object based on distance, orientation, and coordinates.
- Register only one object based on predetermined mathematical calculations.
- Calculate the steering value for navigation using a quadratic function based on the object's distance and position along the x-axis.

###  Serial Communication:
- Send the calculated steering value to the ESP32 via serial communication to adjust the robot's movement accordingly.

---

## Algorithm Explanation

The algorithm begins with image acquisition, where the camera captures real-time images of the track and the surrounding environment. These images are then processed by converting the RGB color space to the HSV (Hue, Saturation, Value) color space, which facilitates better color segmentation. This conversion is crucial for accurately detecting the track lines and objects, as it helps isolate relevant colors regardless of the lighting conditions in the environment.
To reduce noise in the captured frames, Gaussian blur is applied. This blurring operation smooths the image, making the subsequent steps, such as line and object detection, more reliable. After blurring, the algorithm isolates the black border of the track. The black border is then further processed using Canny Edge Detection, a technique that identifies edges in the image, and the Hough Line Transform to detect the boundaries that form the track walls. These steps allow the system to focus only on the track's relevant sections, effectively eliminating irrelevant background data.
Once the black border is identified and masked out, the algorithm proceeds to line detection. Using a predetermined HSV range, the system looks for blue and orange lines that represent the track’s guiding paths. These lines are critical for the robot’s navigation, and the system checks for their presence in the image to determine the robot's position relative to the track.
If either a blue or orange line is found, the algorithm calculates the slope of these lines. Specifically, the algorithm computes the minimum and maximum slopes for both the blue and orange lines (if both are present). These slope values are important for determining the orientation of the robot, as they provide information about whether the robot is traveling in a clockwise or anti-clockwise direction around the track. This step is essential for the robot to navigate turns and adjust its path as needed.
In parallel, the object detection mechanism is employed to identify obstacles within the track’s boundary walls. The detected objects are prioritized based on their distance, orientation, and coordinates within the frame. Using mathematical calculations, the algorithm determines the most relevant object and registers it for navigation. The robot then calculates a steering value using a quadratic function, which takes into account the object's distance and its position along the x-axis. This steering value is crucial for adjusting the robot's movement and ensuring it remains on track while avoiding obstacles.
Finally, the algorithm sends the calculated steering value to the ESP32 through serial communication, which adjusts the robot's movement accordingly. This real-time control ensures that the robot remains on its intended path, whether it's navigating straight sections of the track or making turns to avoid obstacles.
In terms of the underlying processes, the use of HSV conversion enhances the robot's ability to reliably detect track lines in varying lighting conditions, while Gaussian blur reduces noise that could otherwise interfere with detection. Hough Line Transform and Canny Edge Detection are pivotal in accurately identifying track boundaries, allowing for effective masking of the irrelevant parts of the frame. The slope comparison between the detected lines informs the robot's orientation, enabling it to discern whether it's moving clockwise or anti-clockwise on the track. The object prioritization system ensures that only the most relevant obstacles influence the robot’s decisions, optimizing its path-planning efficiency. The final step in the algorithm—the calculation and communication of the steering value—ensures that the robot can make precise, real-time adjustments to its movement.

## **Flowchart**

```mermaid

flowchart TD
    A[Start] --> B[Capture Image]
    B --> O{Object Detected?}

    %% Object Detected Branch
    O -->|Red Object| P[Steer Right with PID]
    O -->|Green Object| Q[Steer Left with PID]
    P --> N[Continue Navigation]
    Q --> N

    %% No Object Detected Branch → Round 1 Logic
    O -->|No| C{Line Detected?}
    
    %% Line Detected = Yes
    C -->|Yes| D{Orientation Set?}
    D -->|Yes| E[Line Count ++]
    D -->|No| F[Fix Orientation for Next Run and Line Count ++]
    E --> G{LineCount >= 12 AND LastLine > 1500ms AND FloorDist < 1500?}
    F --> G
    G -->|Yes| H[Initiate Parking Maneuver]
    G -->|No| K[Use Weighted Average from LIDAR to Find Best Path]

    %% Line Detected = No
    C -->|No| X{LineCount >= 12 AND LastLine > 1500ms AND FloorDist < 1500?}
    X -->|Yes| H
    X -->|No| I[LIDAR Scan Image]
    I --> K
    
    %% Common Path
    K --> M[PID Calculates Steering Value]
    M --> N[Continue Navigation]
```
<p align="center">

>[!IMPORTANT]
The second round has the same code files as first round just instead of the 1st round main code, it has the second round main code and instead of lidar first round, it has lidar second round 

# 2nd round algorithm code explanation:
  ## Lidar Code:

# LidarReader Class Explanation

This Python code defines a `LidarReader` class that is responsible for reading data from a LIDAR sensor, clustering the data points, and calculating the centroid of detected objects in the scan. Below is a breakdown of how it works:

## Key Components

### 1. **Imports**
- **`subprocess`**: To handle the LIDAR sensor process and capture its output.
- **`threading`**: Used to run a background thread to read sensor data in real-time.
- **`re`**: Regular expression to parse data.
- **`math`**: Provides mathematical functions like trigonometric and distance calculations.

### 2. **Global Clustering Parameters**
Global parameters that define constraints for the clustering process:
- `MIN_CLUSTER_POINTS`, `MAX_CLUSTER_POINTS`, etc., control how the code clusters LIDAR points (e.g., the minimum number of points required to form a valid cluster or the maximum allowed cluster width).

### 3. **LidarReader Class**

#### `__init__(self, path, port="/dev/ttyUSB0", baud="460800")`
This method initializes the `LidarReader` object. The `subprocess.Popen` starts the LIDAR sensor process and establishes communication with it using the provided serial port and baud rate. A background thread is also started to read sensor data.

#### `_parse_line(self, line)`
A helper function that reads each line of the sensor output. It uses a regular expression to extract the angle (`ang`) and distance (`dist`) for each data point. It returns these values as a dictionary: `{"ang": <angle>, "dist": <distance>}`.

#### `_read_sensor_output(self)`
Reads output from the LIDAR sensor line-by-line. It decodes the data, parses it with `_parse_line`, and stores the angle-distance pairs in `self.data`, which holds all the sensor measurements as `{angle: distance_mm}`.

#### `get(self, angle)`
Returns the distance (in mm) for a specific angle. If the angle is not found, it returns 0.

#### `get_all(self)`
Returns a full dictionary of all angle-distance pairs collected from the LIDAR sensor.

#### `stop(self)`
Terminates the LIDAR sensor process.

### 4. **Clustering Helpers**

#### `_cluster_max_width(self, cluster)`
Calculates the "width" of a cluster of points. This is the distance between the first and last point in the cluster.

#### `_cluster_centroid(self, cluster)`
Calculates the centroid (average x, y position) of a cluster of points and returns it in meters (since LIDAR points are in mm).

### 5. **`get_clusters(self)`**
This function processes the LIDAR data and identifies clusters:
- It reads all the LIDAR data and starts with an empty `current_cluster`.
- It iterates over the LIDAR scan data (from `scan_range_min` to `scan_range_max` angles) and converts the polar coordinates (angle and distance) to Cartesian coordinates (x, y).
- It then calculates the distance between consecutive points. If the distance exceeds the threshold (`POINT_DIST_THRESH`), the current cluster is saved, and a new cluster begins.
- After finishing the iteration, the function processes the clusters:
    - It checks if each cluster meets the required size and width criteria (`MIN_CLUSTER_WIDTH <= width <= MAX_CLUSTER_WIDTH`).
    - It calculates the centroid and width for each valid cluster and stores the results.

### 6. **Finding the Nearest Cluster**
After clustering, the function identifies the nearest cluster based on its centroid. The nearest cluster is determined by the minimum Euclidean distance from the origin (0, 0) to the centroid of the cluster. It returns the coordinates (centroid) of the nearest cluster, or `(None, None)` if no clusters are found.

## Summary of Process Flow:
1. The `LidarReader` continuously reads data from the LIDAR sensor.
2. The data is parsed and stored in a dictionary with angles as keys and distances as values.
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
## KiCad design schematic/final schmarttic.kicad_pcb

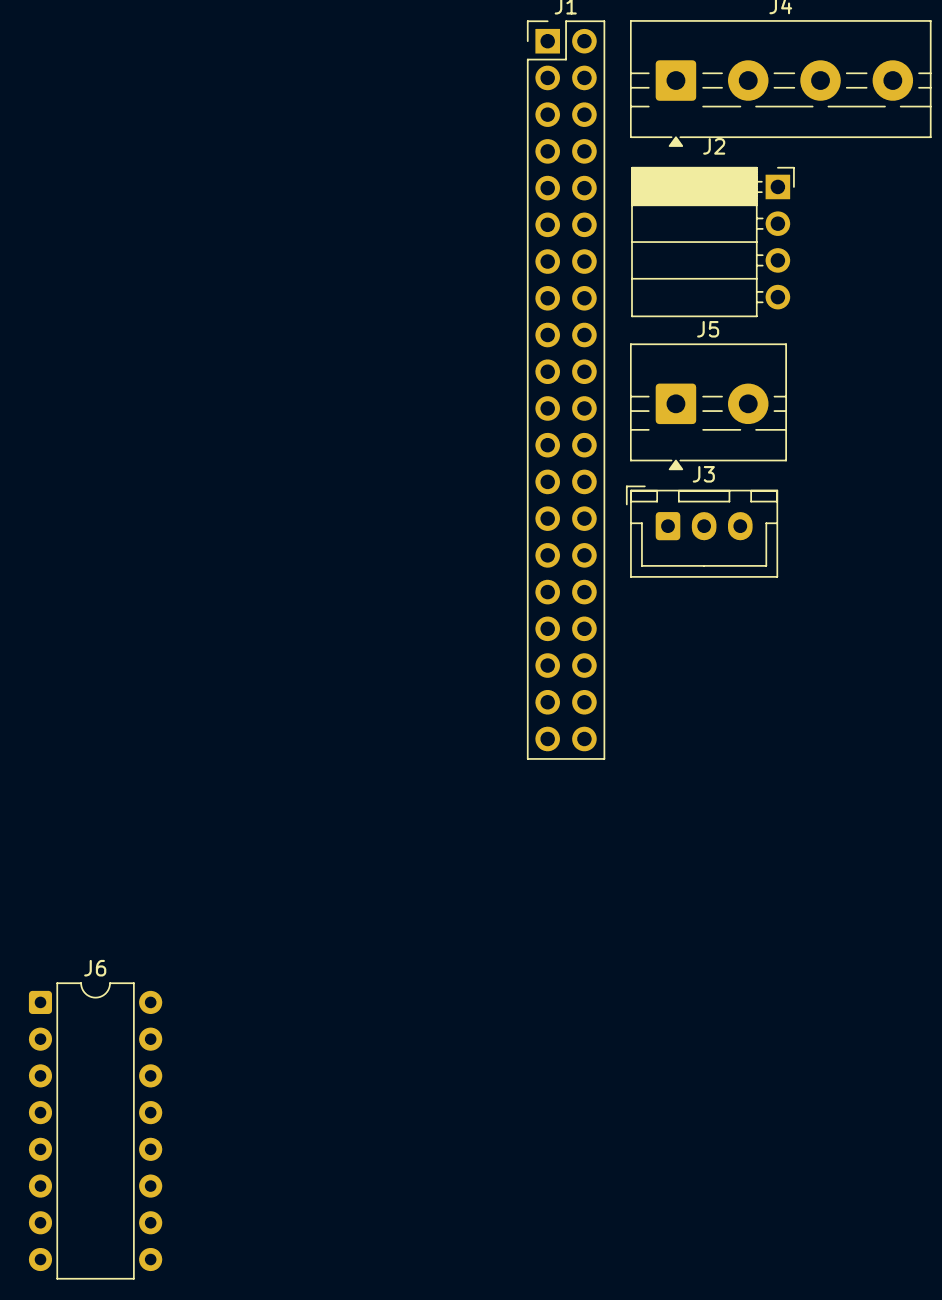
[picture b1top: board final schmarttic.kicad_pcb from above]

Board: 2 copper layers, 6 parts (0 on the bottom side), 8 nets, no tracks yet.

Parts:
J1: rasberry pi; PinHeader_2x20_P2.54mm_Vertical
J2: i2c port for mpu 9250; PinSocket_1x04_P2.54mm_Horizontal
J3: servo motor; JST_XH_B3B-XH-A_1x03_P2.50mm_Vertical
J4: Screw_Terminal_01x04; TerminalBlock_MaiXu_MX126-5.0-04P_1x04_P5.00mm
J5: Screw_Terminal_01x02; TerminalBlock_MaiXu_MX126-5.0-02P_1x02_P5.00mm
J6: Conn_02x08_Counter_Clockwise; DIP-16_W7.62mm

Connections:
unnamed: J1.1, J2.4
unnamed: J1.2, J3.1
unnamed: J1.3, J2.1
unnamed: J1.5, J2.2
unnamed: J1.6, J3.2
unnamed: J1.7, J3.3
unnamed: J1.9, J2.3
unnamed: J4.3, J5.2

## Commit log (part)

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2025-10-04 Update snake animation [skip ci] 670ad64540298b457720a046c855676b084204f8
2025-10-25 Update snake animation [skip ci] e978dfef0480a9ca4bd325639662338bbb770135
